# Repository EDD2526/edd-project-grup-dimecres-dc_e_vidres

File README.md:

View this project on [CADLAB.io](https://cadlab.io/project/30192). 

# Projecte ALÇA-VIDRES

>**Autors:** Àlex Requena , Alfred Abanto
>**Versió:** v3.2

----------

## Objectiu

>PCB per controlar les portes d'un cotxe.
Control de finestres
Controls de seguretat en finestres
Sistema de tancament i obertura de portes
Obertura de portes amb un lector RFID

## Diagrama de blocs

### Descripció/funcionalitat de cada bloc
Microcontrolador PIC24HJ: Cervell del sistema; processa dades i coordina tots els mòduls i comunicacions.

Lector RFID MFRC522: Mòdul de comunicació sense contacte per a identificació de targetes via interfície SPI.

Polsadors B3F: Interfície d'usuari per a l'activació manual de funcions del sistema.

Transceptor CAN TJA1051: Interfície de comunicació robusta per a l'enviament de dades a llarga distància.

Pont H L298N: Driver de potència per controlar el gir i la velocitat de dos motors DC.

Amp. Op. MCP6022: Condiciona senyals analògics (com el consum dels motors) per a una lectura precisa del micro.

Final de carrera SS-01GL111-ET: Sensor mecànic de seguretat que detecta el límit de moviment físic.

Conversor TSR 2-2450: Transforma eficientment els 12V de la bateria en 5V estables.

Regulador LM1117-3.3: Redueix els 5V a 3.3V per alimentar la lògica i els xips de control.
## Requisits / Especificacions

----

## Components

| Descripci&#243; | Ref | Package |Datasheet | Prove&#239;dor | Preu | Unitats |
| Driver de Motor (Puente H) | L298N | TO-220-15 | [Datasheet](https://www.alldatasheet.com/datasheet-pdf/view/22440/STMICROELECTRONICS/L298N.html) | [Mouser](https://www.mouser.es/c/?q=L298N) | 10.31 &euro; | 1x |

| Convertidor DC-DC | TSR2-2450 | SIP-3 | https://www.tracopower.com/products/tsr2.pdf | https://www.mouser.es/c/?q=TSR2-2450 | 10.41 € | 1x |

| Amplificador Op. | MCP6022 | SOIC-8 | [Datasheet](https://www.alldatasheet.com/datasheet-pdf/view/99099/MICROCHIP/MCP6022.html) | [Mouser](https://www.mouser.es/c/?q=MCP6022) | 1.53 &euro; | 1x |
-----------
| Regulador LDO | LM1117DT-3.3 | TO-252 | https://www.ti.com/lit/ds/symlink/lm1117.pdf | https://www.mouser.es/c/?q=LM1117DT-3.3 | 1.5 € | 1x |
| Lector RFID | MFRC52201HN1_157 | HVQFN-32 | https://www.nxp.com/docs/en/data-sheet/MFRC522.pdf | https://www.mouser.es/c/?q=MFRC52201HN1_157 | 6.8€ | 1x |

| Microcontrolador | PIC24HJ64GP504-I/PT | TQFP-44 | https://ww1.microchip.com/downloads/en/DeviceDoc/70293G.pdf | https://www.mouser.es/c/?q=PIC24HJ64GP504-I/PT | 5.75 € | 1x |

| Transceptor CAN | SN65HVD230 | SOIC-8 | https://www.ti.com/lit/ds/symlink/sn65hvd230.pdf | https://www.mouser.es/c/?q=SN65HVD230 | 1.91 € | 1x |

| Ferrita | FerriteBead | SMD 0805 | https://www.vishay.com/docs/34025/ilbb0805.pdf| [Mouser](https://www.mouser.es/c/?q=Ferrite%20Bead%200805) | 0.08 &euro; | 1x |

| Conector D-Sub 9 | A-DF 09 LL/Z | THT | https://www.assmann-wsw.com/fileadmin/datasheets/ASS_0212_CO.pdf | https://www.mouser.es/c/?q=A-DF+09+LL%2FZ | 2.18 € | 2x |
## Software
Kicad
### Eines:

  * KiCad 10.0 

### Funcionalitats:
Controlar finestres.

Controls de seguretat en finestres.

Sistema de tancament i obertura de portes.

Obrir portes amb un lector RFID.

-----------

## Historial de canvis
|11/03| Alfred | Main | v0.0 | Diagrama de blocs i 
components |
|18/03| Àlex | Main | v0.1 | Esquemàtic i simulacions |
| 25/03| Àlex | Main | v1 | layoutv1|
| 10/04| Alfred | Main | v2 | layoutv2, dues etapes|
| 10/04| Alfred | Main | v3.0 | layoutv2, redistribució|
| 22/04| Àlex | Main | v3.1 | layoutv3, errors arreglats|
| 27/04| Àlex i Alfred | Main | v3.2| layoutv3, layout final|

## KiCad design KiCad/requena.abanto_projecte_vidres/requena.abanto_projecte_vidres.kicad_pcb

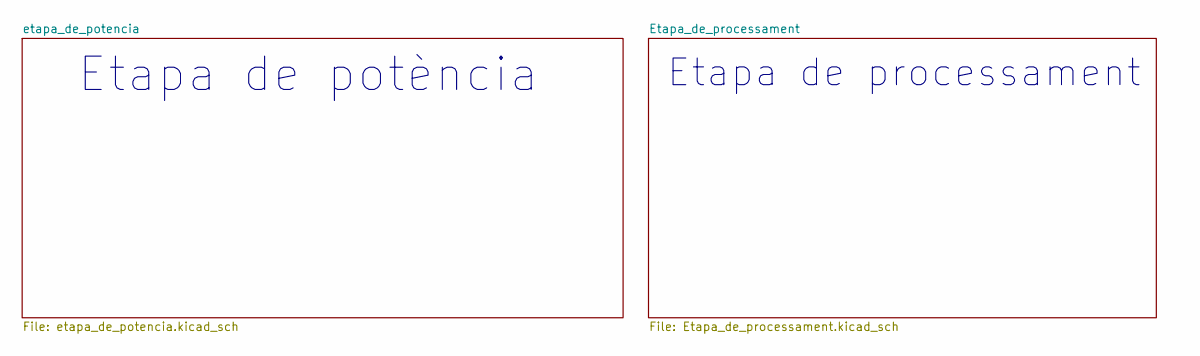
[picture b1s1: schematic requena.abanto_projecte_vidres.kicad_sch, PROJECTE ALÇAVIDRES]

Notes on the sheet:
Etapa de processament
Etapa de potència

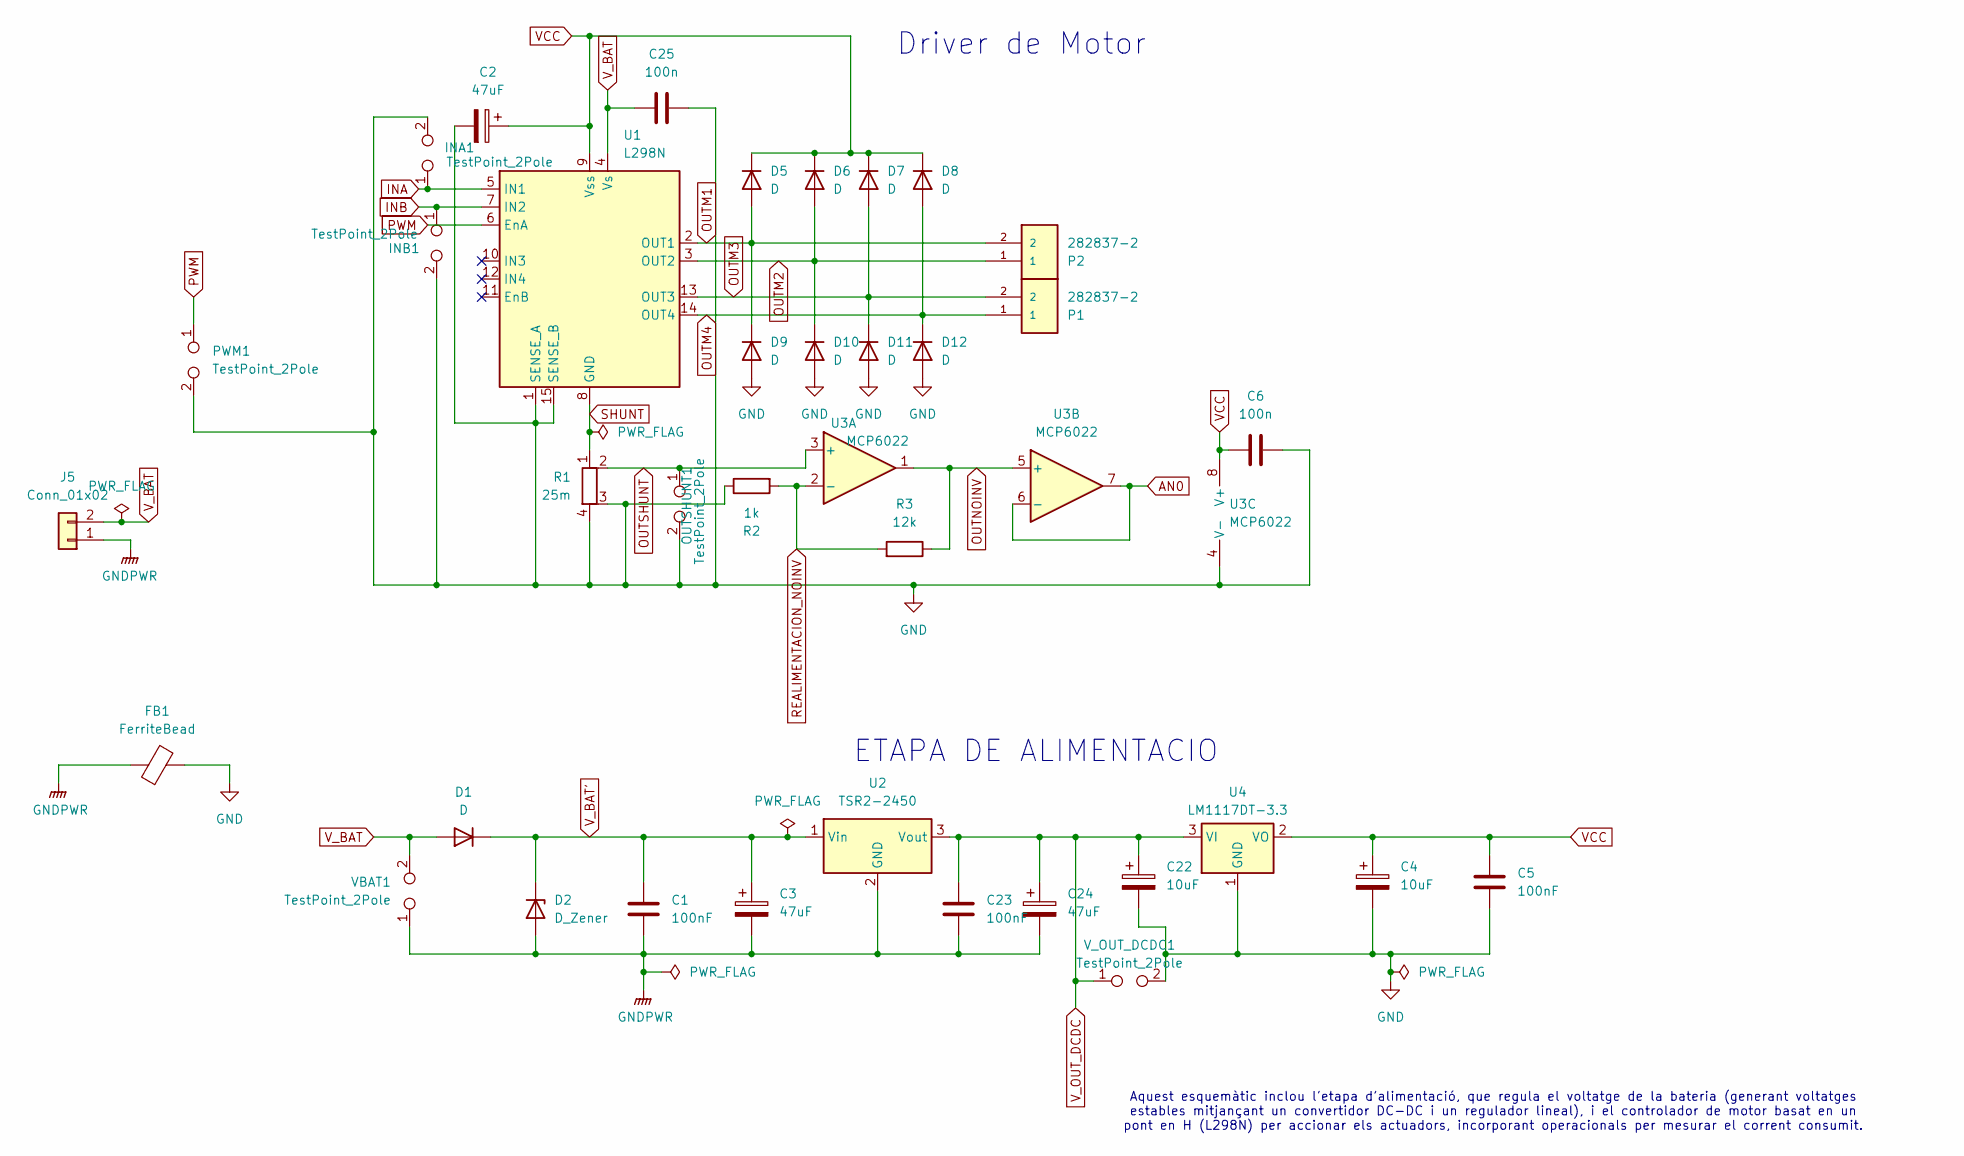
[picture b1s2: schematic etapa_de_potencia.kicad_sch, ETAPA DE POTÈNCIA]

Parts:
C1, C5, C23: 100nF; C_0805_2012Metric
C2, C3, C24: 47uF; CP_Radial_D4.0mm_P1.50mm
C4, C22: 10uF; CP_Radial_D4.0mm_P1.50mm
C6, C25: 100n; C_0603_1608Metric
D1: D; D_DO-41_SOD81_P12.70mm_Horizontal
D2: D_Zener; D_A-405_P2.54mm_Vertical_AnodeUp
D5, D6, D7, D8, D9, D10, D11, D12: D; D_DO-201AD_P15.24mm_Horizontal
FB1: FerriteBead; L_0805_2012Metric
INA1: TestPoint_2Pole; TestPoint_2Pads_Pitch2.54mm_Drill0.8mm
INB1: TestPoint_2Pole; TestPoint_2Pads_Pitch2.54mm_Drill0.8mm
J5: Conn_01x02; TerminalBlock_Xinya_XY308-2.54-2P_1x02_P2.54mm_Horizontal
OUTSHUNT1: TestPoint_2Pole; TestPoint_2Pads_Pitch2.54mm_Drill0.8mm
P1, P2: 282837-2; TE_282837-2; PARTREV G3
PWM1: TestPoint_2Pole; TestPoint_2Pads_Pitch2.54mm_Drill0.8mm
R1: 25m; R_Shunt_Vishay_WSK2512_6332Metric_T1.19mm
R2: 1k; R_1206_3216Metric
R3: 12k; R_1206_3216Metric
U1: L298N; TO-220-15_P2.54x5.08mm_StaggerOdd_Lead4.58mm_Vertical
U2: TSR2-2450; Converter_DCDC_TRACO_TSR2-xxxx_THT
U3: MCP6022; SOIC-8_3.9x4.9mm_P1.27mm
U4: LM1117DT-3.3; TO-252-2
VBAT1: TestPoint_2Pole; TestPoint_2Pads_Pitch2.54mm_Drill0.8mm
V_OUT_DCDC1: TestPoint_2Pole; TestPoint_2Pads_Pitch2.54mm_Drill0.8mm

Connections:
AN0: U3.6 (-), U3.7; also elsewhere on the board
GNDPWR: C1.2, C3.2, C23.2, C24.2, D2.2 (A), FB1.1, J5.1, U2.2 (GND), VBAT1.1
INA: INA1.1, U1.5 (IN1); also elsewhere on the board
INB: INB1.1, U1.7 (IN2); also elsewhere on the board
OUTM1: D5.2 (A), D9.1 (K), P2.2, U1.2 (OUT1)
OUTM2: D6.2 (A), D10.1 (K), P2.1, U1.3 (OUT2)
OUTM3: D7.2 (A), D11.1 (K), P1.2, U1.13 (OUT3)
OUTM4: D8.2 (A), D12.1 (K), P1.1, U1.14 (OUT4)
OUTNOINV: R3.1, U3.1, U3.5 (+)
OUTSHUNT: OUTSHUNT1.1, R1.2, U3.3 (+)
PWM: PWM1.1, U1.6 (EnA); also elsewhere on the board
REALIMENTACION_NOINV: R2.2, R3.2, U3.2 (-)
SHUNT: R1.1, U1.8 (GND)
VCC: C2.1, C4.1, C5.1, C6.1, D5.1 (K), D6.1 (K), D7.1 (K), D8.1 (K), U1.9 (Vss), U3.8 (V+), U4.2 (VO); also elsewhere on the board
V_BAT: C25.1, D1.2 (A), J5.2, U1.4 (Vs), VBAT1.2
V_BAT': C1.1, C3.1, D1.1 (K), D2.1 (K), U2.1 (Vin)
V_OUT_DCDC: C22.1, C23.1, C24.1, U2.3 (Vout), U4.3 (VI), V_OUT_DCDC1.1

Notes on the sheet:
Aquest esquemàtic inclou l'etapa d'alimentació, que regula el voltatge de la bateria (generant voltatges estables mitjançant un convertidor DC-DC i un regulador lineal), i el controlador de motor basat en un pont en H (L298N) per accionar els actuadors, incorporant operacionals per mesurar el corre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
Driver de Motor
ETAPA DE ALIMENTACIO

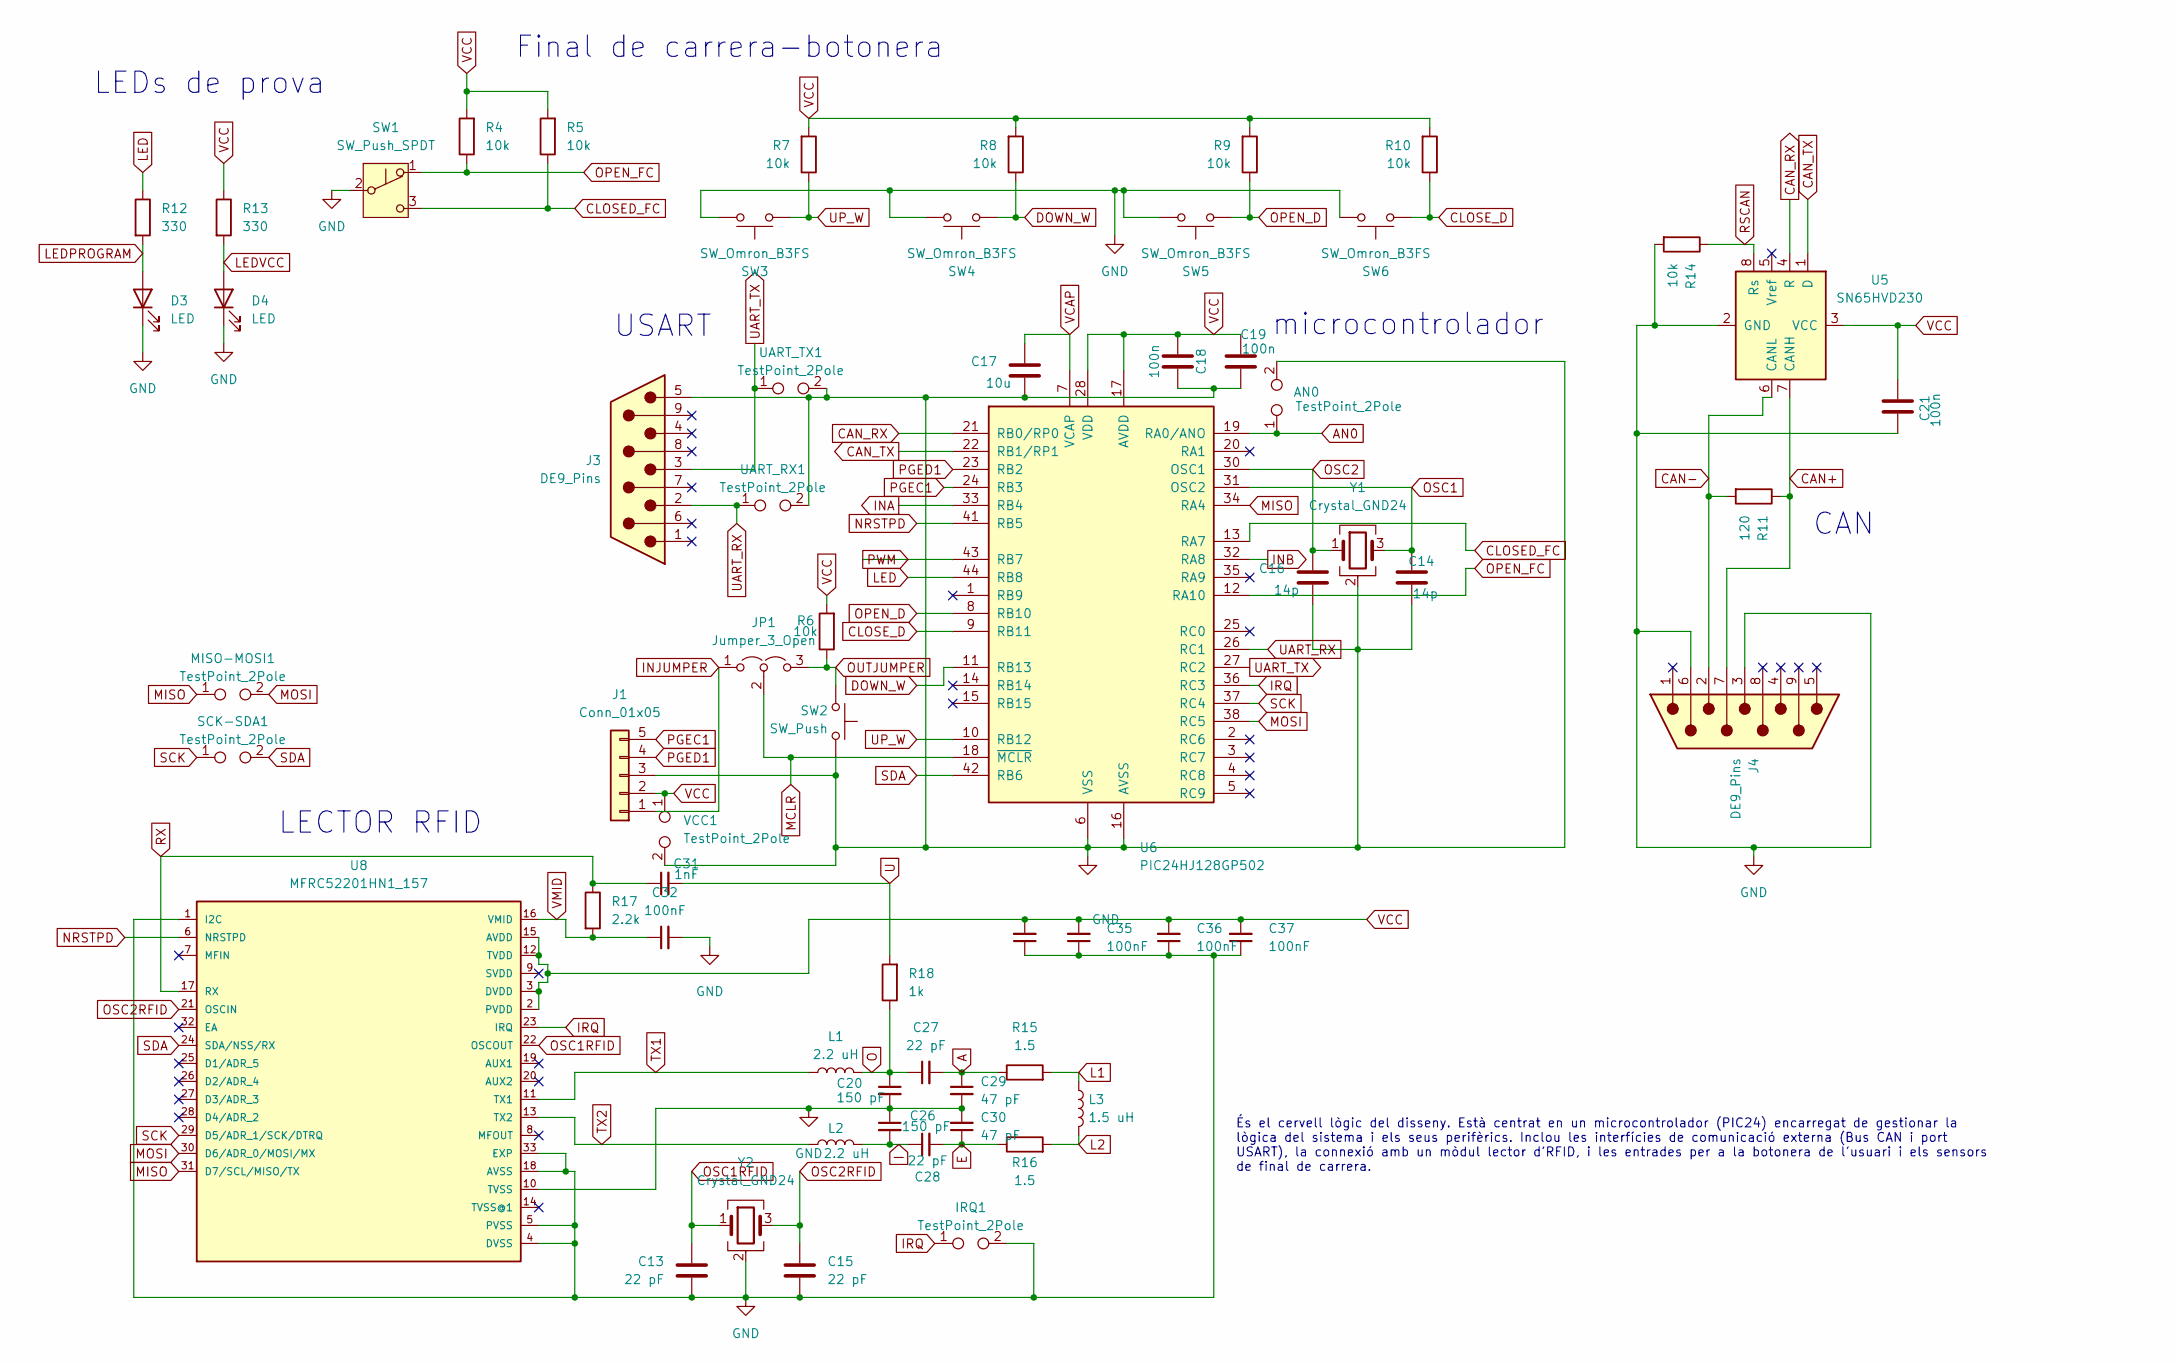
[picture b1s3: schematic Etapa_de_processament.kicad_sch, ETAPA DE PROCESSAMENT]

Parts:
AN0: TestPoint_2Pole; TestPoint_2Pads_Pitch2.54mm_Drill0.8mm
C13, C15: 22 pF; C_0805_2012Metric
C14, C16: 14p; C_0805_2012Metric
C17: 10u; C_0603_1608Metric
C18, C19, C21: 100n; C_0603_1608Metric
C20, C26: 150 pF; C_1206_3216Metric
C27, C28: 22 pF; C_1206_3216Metric
C29, C30: 47 pF; C_1206_3216Metric
C31: 1nF; C_1206_3216Metric
C32: 100nF; C_1206_3216Metric
C34, C35, C36, C37: 100nF; C_0603_1608Metric
D3, D4: LED; D_0805_2012Metric
IRQ1: TestPoint_2Pole; TestPoint_2Pads_Pitch2.54mm_Drill0.8mm
J1: Conn_01x05; PinHeader_1x05_P2.54mm_Vertical
J3, J4: DE9_Pins; DSUB-9_Pins_Horizontal_P2.77x2.54mm_EdgePinOffset9.40mm
JP1: Jumper_3_Open; PinHeader_1x03_P2.54mm_Vertical
L1, L2: 2.2 uH; L_1206_3216Metric
L3: 1.5 uH; L_1206_3216Metric
MISO-MOSI1: TestPoint_2Pole; TestPoint_2Pads_Pitch2.54mm_Drill0.8mm
R4, R5, R6, R7, R8, R9, R10, R14: 10k; R_1206_3216Metric
R11: 120; R_1206_3216Metric
R12, R13: 330; R_1206_3216Metric
R15, R16: 1.5; R_1206_3216Metric
R17: 2.2k; R_1206_3216Metric
R18: 1k; R_1206_3216Metric
SCK-SDA1: TestPoint_2Pole; TestPoint_2Pads_Pitch2.54mm_Drill0.8mm
SW1: SW_Push_SPDT; SW_SPDT_PCM12
SW2: SW_Push; SW_SPST_Omron_B3FS-100xP
SW3, SW4, SW5, SW6: SW_Omron_B3FS; SW_SPST_Omron_B3FS-100xP
U5: SN65HVD230; SOIC-8_3.9x4.9mm_P1.27mm
U6: PIC24HJ128GP502; TQFP-44_10x10mm_P0.8mm
U8: MFRC52201HN1_157; QFN50P500X500X100-33N
UART_RX1: TestPoint_2Pole; TestPoint_2Pads_Pitch2.54mm_Drill0.8mm
UART_TX1: TestPoint_2Pole; TestPoint_2Pads_Pitch2.54mm_Drill0.8mm
VCC1: TestPoint_2Pole; TestPoint_2Pads_Pitch2.54mm_Drill0.8mm
Y1: Crystal_GND24; Crystal_SMD_3225-4Pin_3.2x2.5mm
Y2: Crystal_GND24; Crystal_SMD_2520-4Pin_2.5x2.0mm

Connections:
A: C27.2, C29.1, R15.1
AN0: AN0.1, U6.19 (RA0/ANO); also elsewhere on the board
CAN+: J4.7, R11.1, U5.7 (CANH)
CAN-: J4.2, R11.2, U5.6 (CANL)
CAN_RX: U5.4 (R), U6.21 (RB0/RP0)
CAN_TX: U5.1 (D), U6.22 (RB1/RP1)
CLOSED_FC: R5.1, SW1.3 (C), U6.13 (RA7)
CLOSE_D: R10.1, U6.9 (RB11); also elsewhere on the board
DOWN_W: R8.1, U6.11 (RB13); also elsewhere on the board
E: C28.2, C30.1, R16.1
I: C26.2, C28.1, L2.2
INA: U6.33 (RB4); also elsewhere on the board
INB: U6.32 (RA8); also elsewhere on the board
INJUMPER: J1.1, JP1.1 (A)
IRQ: IRQ1.1, U6.36 (RC3), U8.23 (IRQ)
L1: L3.1, R15.2
L2: L3.2, R16.2
LED: R12.1, U6.44 (RB8)
LEDPROGRAM: D3.2 (A), R12.2
LEDVCC: D4.2 (A), R13.2
MCLR: JP1.2 (C), U6.18 (~MCLR)
MISO: MISO-MOSI1.1, U6.34 (RA4), U8.31 (D7/SCL/MISO/TX)
MOSI: MISO-MOSI1.2, U6.38 (RC5), U8.30 (D6/ADR_0/MOSI/MX)
NRSTPD: U6.41 (RB5), U8.6 (NRSTPD)
O: C20.1, C27.1, L1.2, R18.1
OPEN_D: R9.1, U6.8 (RB10); also elsewhere on the board
OSC1: C14.1, U6.31 (OSC2), Y1.3
OSC1RFID: C13.1, U8.22 (OSCOUT), Y2.1
OSC2: C16.1, U6.30 (OSC1), Y1.1
OSC2RFID: C15.1, U8.21 (OSCIN), Y2.3
OUTJUMPER: JP1.3 (B), R6.1; also elsewhere on the board
PGEC1: J1.5, U6.24 (RB3)
PGED1: J1.4, U6.23 (RB2)
PWM: U6.43 (RB7); also elsewhere on the board
RSCAN: R14.1, U5.8 (Rs)
RX: C31.1, R17.1, U8.17 (RX)
SCK: SCK-SDA1.1, U6.37 (RC4), U8.29 (D5/ADR_1/SCK/DTRQ)
SDA: SCK-SDA1.2, U6.42 (RB6), U8.24 (SDA/NSS/RX)
TX1: L1.1, U8.11 (TX1)
TX2: L2.1, U8.13 (TX2)
U: C31.2, R18.2
UART_RX: J3.2, U6.26 (RC1), UART_RX1.1
UART_TX: J3.3, U6.27 (RC2), UART_TX1.1
VCAP: C17.1, U6.7 (VCAP)
VCC: C18.2, C19.1, C21.1, C34.2, C35.2, C36.2, C37.2, J1.2, R4.2, R5.2, R6.2, R7.2, R8.2, R9.2, R10.2, R13.1, U5.3 (VCC), U6.17 (AVDD), U6.28 (VDD), U6.40 (VDD), U8.2 (PVDD), U8.3 (DVDD), U8.12 (TVDD), U8.15 (AVDD), VCC1.1; also elsewhere on the board
VMID: C32.1, R17.2, U8.16 (VMID)

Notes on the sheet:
CAN
LEDs de prova
LECTOR RFID
microcontrolador
USART
Final de carrera-botonera
És el cervell lògic del disseny. Està centrat en un microcontrolador (PIC24) encarregat de gestionar la lògica del sistema i els seus perifèrics. Inclou les interfícies de comunicació externa (Bus CAN i port USART), la connexió amb un mòdul lector d'RFID, i les entrades per a la botonera de l'usuar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

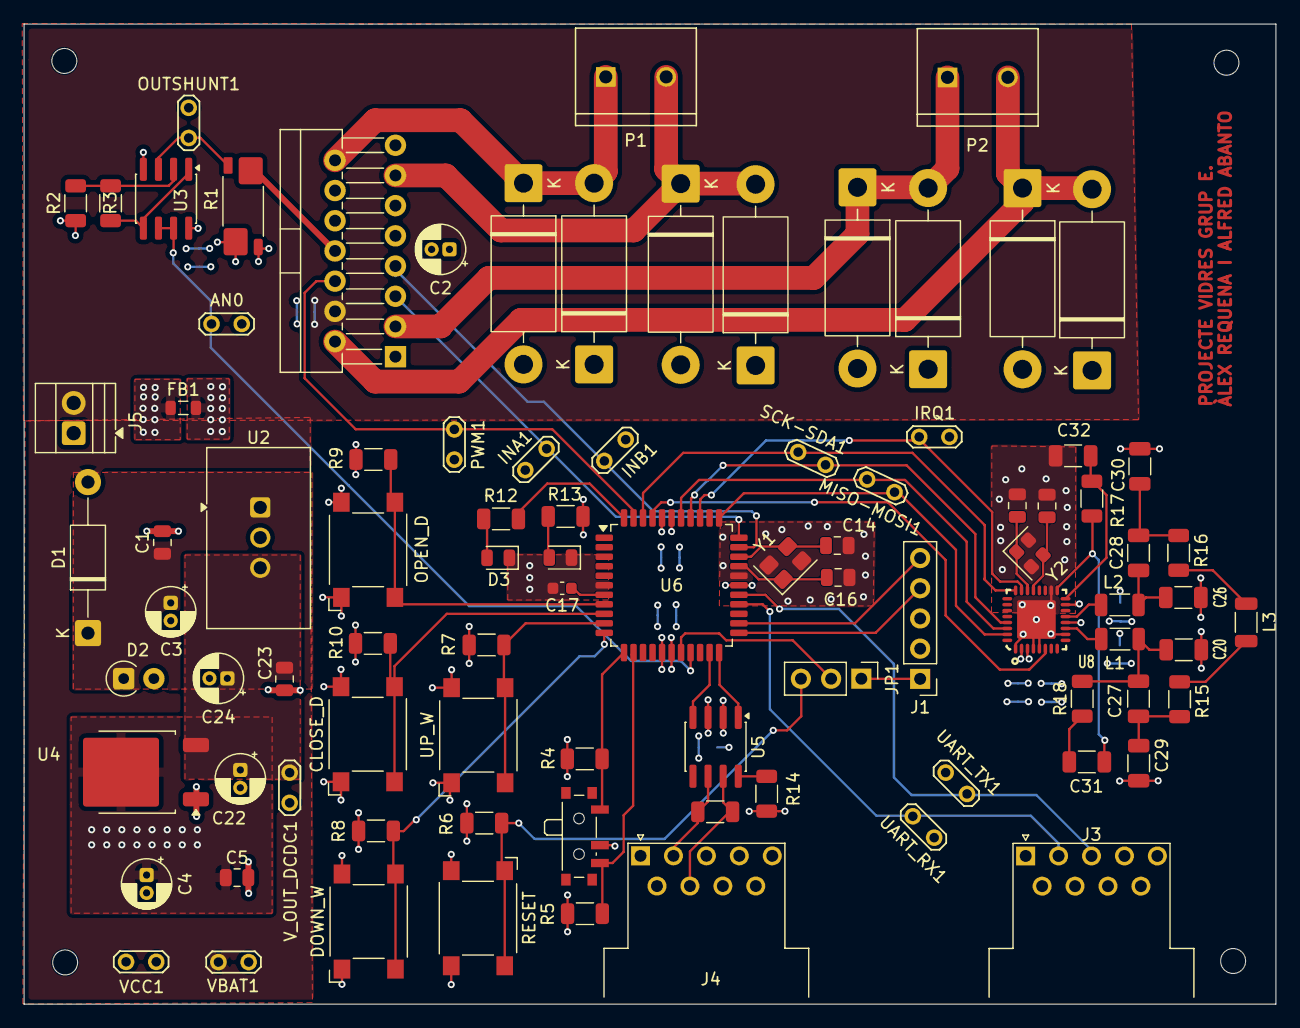
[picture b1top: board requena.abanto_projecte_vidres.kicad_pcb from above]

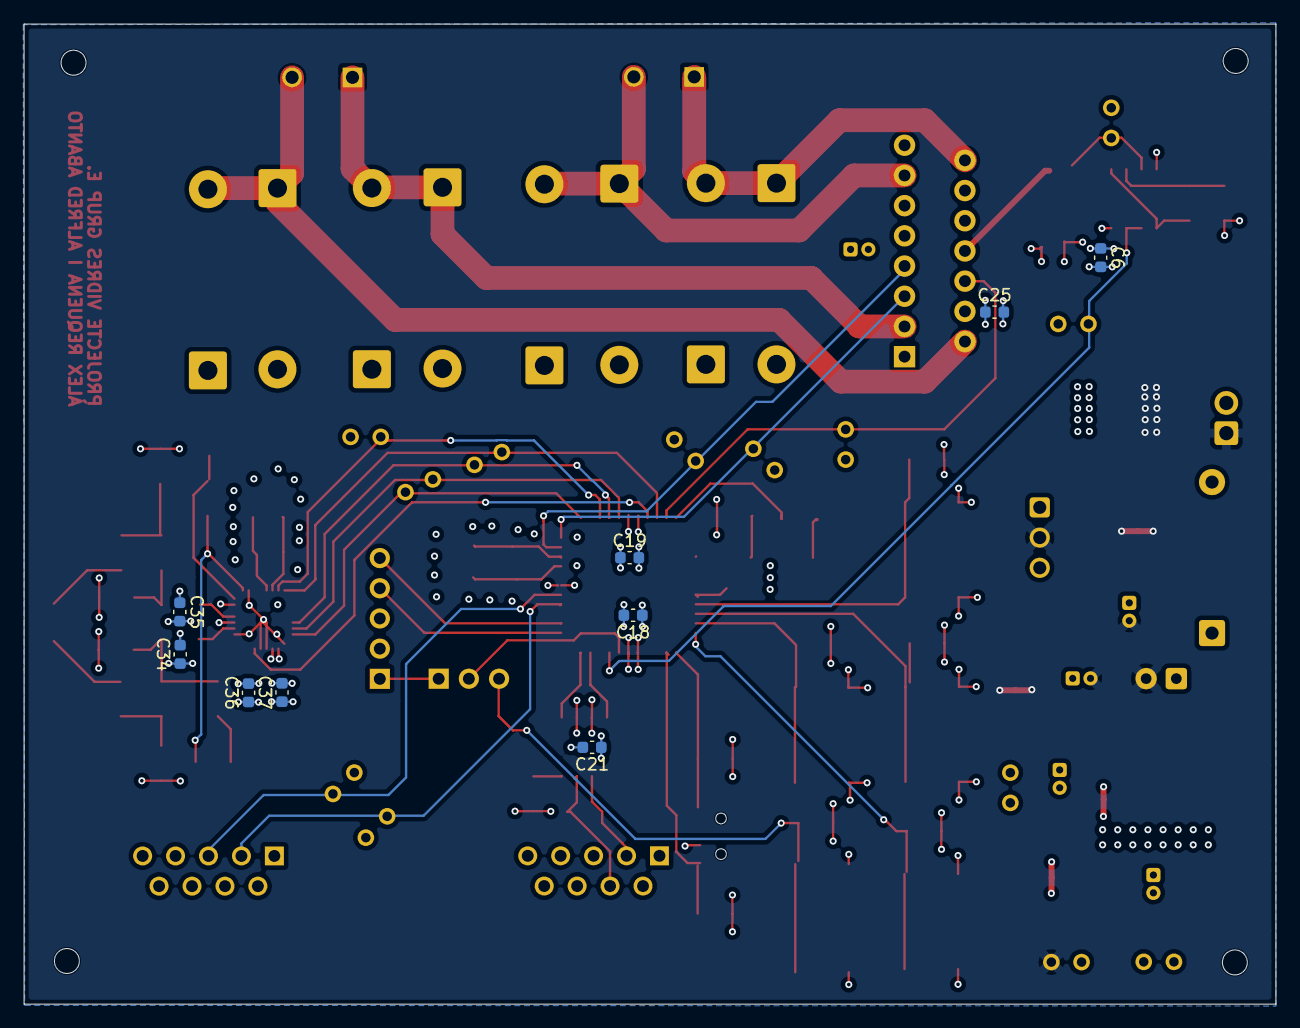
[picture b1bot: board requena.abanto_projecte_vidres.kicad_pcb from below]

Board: 4 copper layers, 105.3 x 82.4 mm, 99 parts (9 on the bottom side), 61 nets.

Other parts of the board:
CLOSE_D: SW_Omron_B3FS; SW_SPST_Omron_B3FS-100xP
DOWN_W: SW_Omron_B3FS; SW_SPST_Omron_B3FS-100xP
OPEN_D: SW_Omron_B3FS; SW_SPST_Omron_B3FS-100xP
RESET: SW_Push; SW_SPST_Omron_B3FS-100xP
UP_W: SW_Omron_B3FS; SW_SPST_Omron_B3FS-100xP

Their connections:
CLOSE_D: CLOSE_D.2; also elsewhere on the board
DOWN_W: DOWN_W.2; also elsewhere on the board
OPEN_D: OPEN_D.2; also elsewhere on the board
OUTJUMPER: RESET.1; also elsewhere on the board

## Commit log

2026-03-11 autors afegits a readme
2026-03-11 creacion proyecto kikad
2026-03-12 Creacio d'etapes
2026-03-14 etapa alimentación empezada
2026-03-15 avance can
2026-03-15 avance etapa-de-processament
2026-03-15 He ficar un led
2026-03-15 avance comunicaciones
2026-03-15 posar etiquetes
2026-03-15 comunicaciones
2026-03-15 millora
2026-03-15 millora circuit
2026-03-15 proteccion alimentacion
2026-03-15 avance sensores
2026-03-15 avance etapa de potencia
2026-03-15 arreglos
2026-03-16 clase
2026-03-16 cambios de clase
2026-03-16 arreglos :)
2026-03-16 Backlink to CADLAB.io has been added.
2026-03-17 saywallahibro,canvis
2026-03-17 millora el esquematic
2026-03-22 Millora projecte 1
2026-03-22 guardado
2026-03-22 cambios
2026-03-22 correcions
2026-03-23 millora_petjades
2026-03-24 milora_esquema_i_layoutcomençat
2026-04-05 Millora del micro a 44 pins
2026-04-05 esquema acabat
2026-04-05 a mimir
2026-04-06 primera pcb
2026-04-06 Avenç de placement
2026-04-06 alfred guapo
2026-04-08 placement pcb
2026-04-09 ficat diodes de proteccion driver
2026-04-09 foking diodos
2026-04-09 pierreiedgarilofu
2026-04-09 buenas noches alfred
2026-04-10 Placement més o menys colocat, i avenç de algunes connexions
2026-04-11 el RFID me jodio la vida
2026-04-11 viva el peru
2026-04-12 hamza zibar
2026-04-15 regles de disseny i més coses
2026-04-19 hola alfred
2026-04-19 he posat una petjada i simbol
2026-04-19 bomboclat walahi
2026-04-19 v2placement
2026-04-21 joan canals el mejor
2026-04-24 algunes millores
2026-04-25 faltan tests points
2026-04-25 alfred butanero
2026-04-26 huellas arregladas
2026-04-28 alfred masoquista
